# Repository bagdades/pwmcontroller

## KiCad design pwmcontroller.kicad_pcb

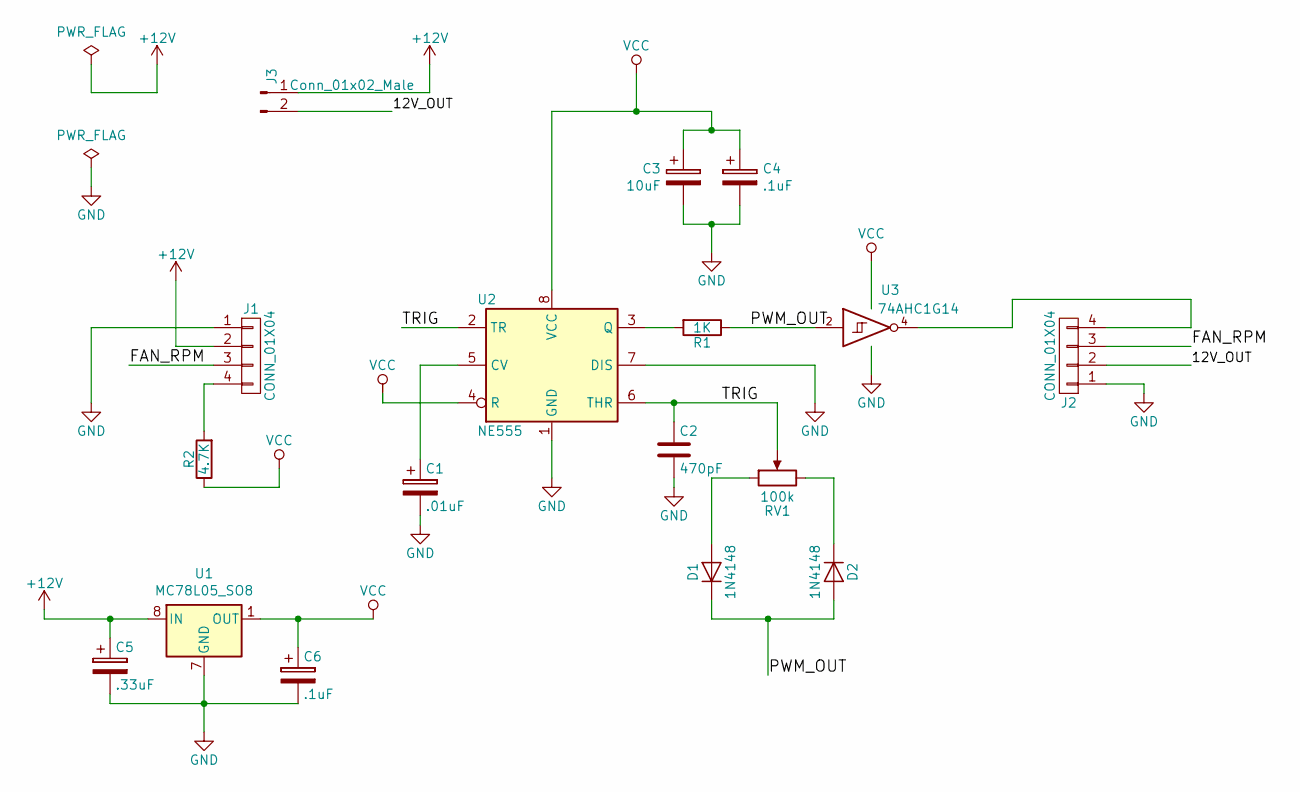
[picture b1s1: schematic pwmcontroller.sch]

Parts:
C1: .01uF; C_0805_2012Metric
C2: 470pF; C_0805_2012Metric
C3: 10uF; CP_Radial_D5.0mm_P2.50mm
C4, C6: .1uF; C_0805_2012Metric
C5: .33uF; CP_Radial_D5.0mm_P2.50mm
D1, D2: 1N4148; D_SOD-123
J1, J2: CONN_01X04; Molex_KK-254_AE-6410-04A_1x04_P2.54mm_Vertical
J3: Conn_01x02_Male; PinHeader_1x02_P2.54mm_Vertical
R1: 1K; R_0805_2012Metric
R2: 4.7K; R_0805_2012Metric
RV1: 100k; Potentiometer_Alpha_RD901F-40-00D_Single_Vertical_CircularH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
U1: MC78L05_SO8; SOIC-8_3.9x4.9mm_P1.27mm
U2: NE555; DIP-8_W7.62mm
U3: 74AHC1G14; SOT-23-5

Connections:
+12V: C5.1, J1.2, J3.1, U1.8 (IN)
/12V_OUT: J2.2, J3.2
/FAN_RPM: J1.3, J2.3
/PWM_OUT: D1.1 (K), D2.2 (A), R1.1, U3.2
/TRIG: C2.1, RV1.2, U2.2 (TR), U2.6 (THR)
GND: C1.2, C2.2, C3.2, C4.2, C5.2, C6.2, J1.1, J2.1, U1.2 (GND), U1.3 (GND), U1.6 (GND), U1.7 (GND), U2.1 (GND), U2.7 (DIS), U3.3 (GND)
unnamed: C1.1, U2.5 (CV)
unnamed: D1.2 (A), RV1.1
unnamed: D2.1 (K), RV1.3
unnamed: J1.4, R2.2
unnamed: J2.4, U3.4
unnamed: R1.2, U2.3 (Q)
VCC: C3.1, C4.1, C6.1, R2.1, U1.1 (OUT), U2.4 (R), U2.8 (VCC), U3.5 (VCC)

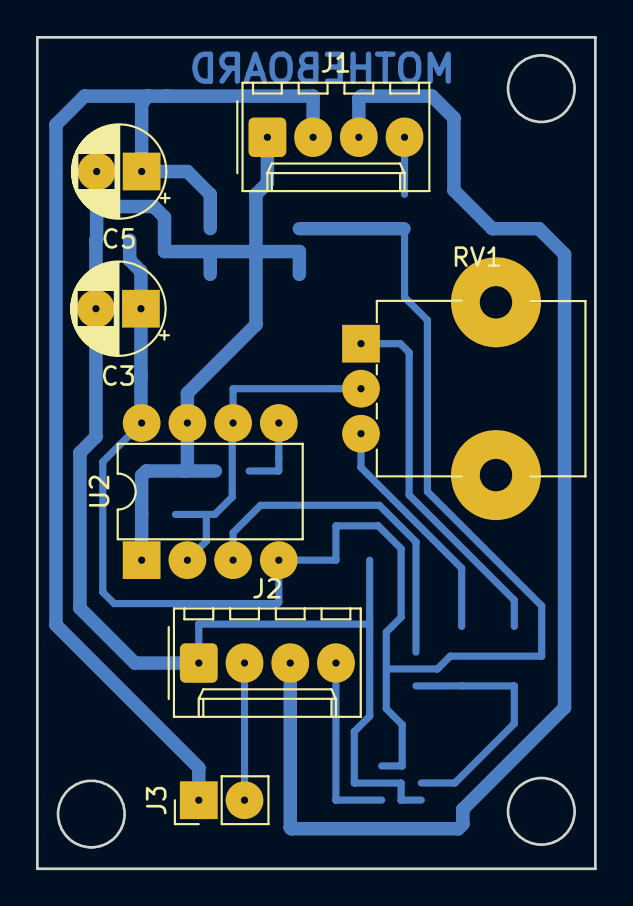
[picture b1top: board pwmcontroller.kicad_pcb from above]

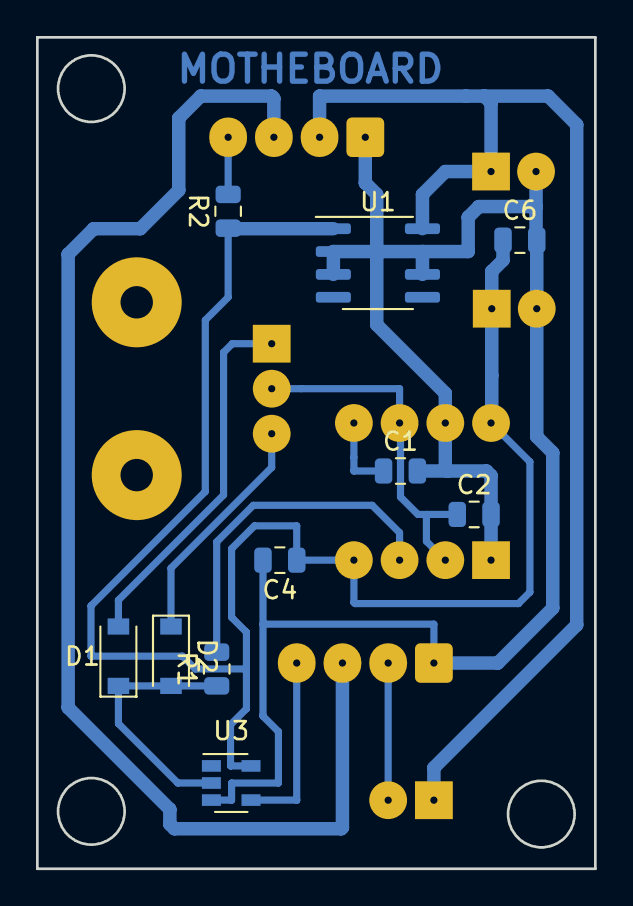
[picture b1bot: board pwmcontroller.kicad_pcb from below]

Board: 2 copper layers, 31.0 x 46.2 mm, 17 parts (10 on the bottom side), 13 nets.

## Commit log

2019-09-15 Two commit
